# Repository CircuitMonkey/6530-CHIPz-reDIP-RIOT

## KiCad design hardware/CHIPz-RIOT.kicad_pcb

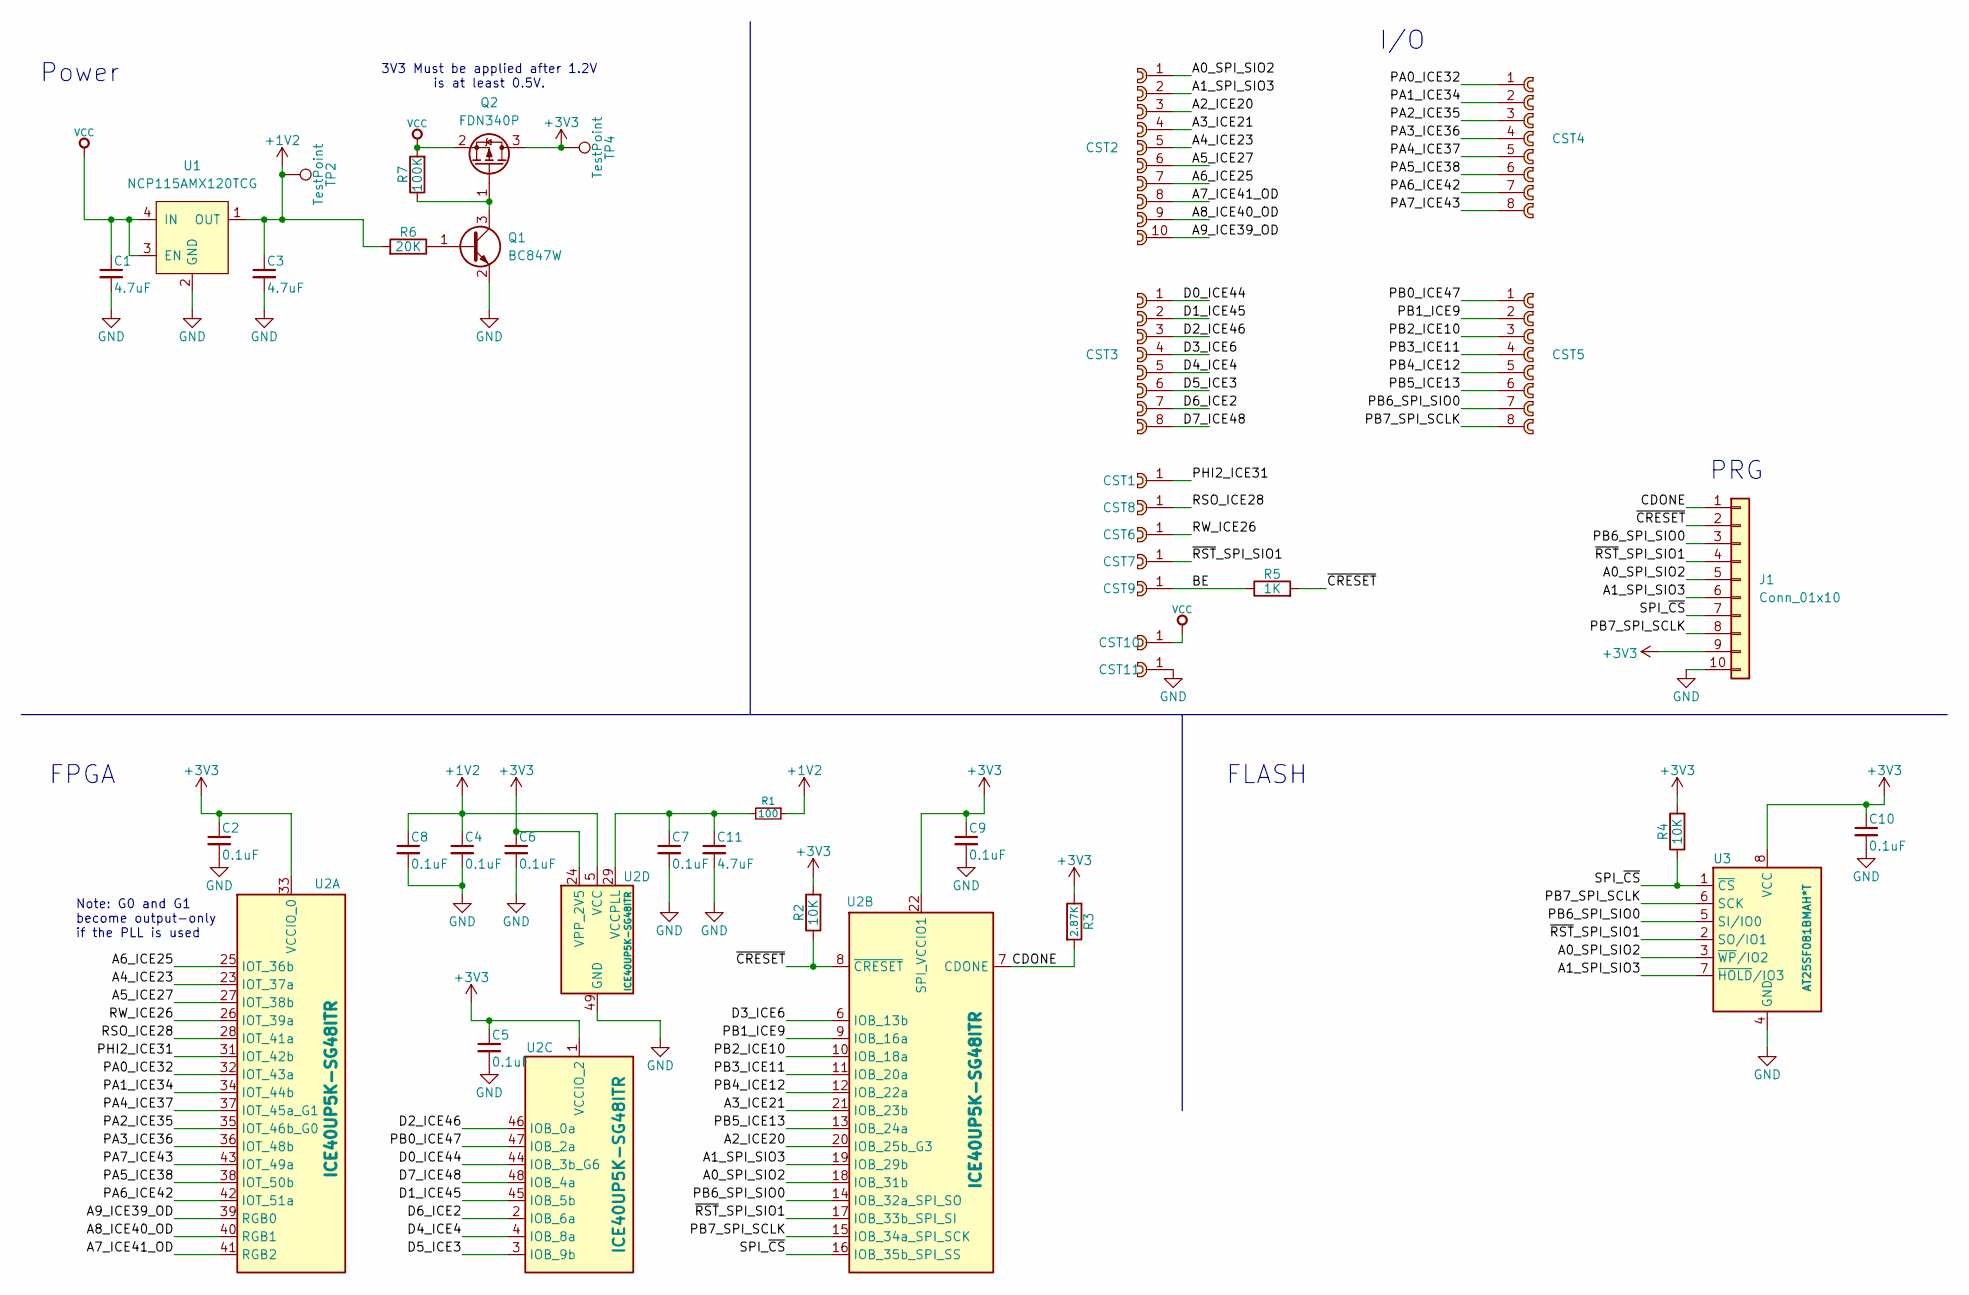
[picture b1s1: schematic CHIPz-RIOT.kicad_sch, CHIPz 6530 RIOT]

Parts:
C1, C3, C11: 4.7uF; C_0402_1005Metric_Pad0.74x0.62mm_HandSolder
C2, C4, C5, C6, C7, C8, C9, C10: 0.1uF; C_0402_1005Metric_Pad0.74x0.62mm_HandSolder
CST1, CST6, CST7, CST8, CST9, CST10, CST11: cast-2.0-01P
CST2: cast-2.0-10P
CST3, CST4, CST5: cast-2.0-08P
J1: Conn_01x10; JST_SHL_SM10B-SHLS-TF_1x10-1MP_P1.00mm_Horizontal
Q1: BC847W; SOT-323_SC-70
Q2: FDN340P; SOT-23
R1: 100; R_0402_1005Metric_Pad0.72x0.64mm_HandSolder
R2, R4: 10K; R_0402_1005Metric_Pad0.72x0.64mm_HandSolder
R3: 2.87K; R_0402_1005Metric_Pad0.72x0.64mm_HandSolder
R5: 1K; R_0402_1005Metric_Pad0.72x0.64mm_HandSolder
R6: 20K; R_0402_1005Metric_Pad0.72x0.64mm_HandSolder
R7: 100K; R_0402_1005Metric_Pad0.72x0.64mm_HandSolder
TP2, TP4: TestPoint; TestPoint_Pad_D1.00mm
U1: NCP115AMX120TCG; CASE_711AJ_1.0x1.0mm_P0.65mm
U2: ICE40UP5K-SG48ITR; QFN-48-1EP_7x7mm_P0.5mm_EP5.6x5.6mm
U3: AT25SF081BMAH*T; UDFN-8_EP_3x2_Pitch0.5mm

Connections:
+1V2: C3.1, C4.1, C8.1, R1.1, R6.2, TP2.1, U1.1 (OUT), U2.5 (VCC), U2.30 (VCC)
+3V3: C2.1, C5.1, C6.1, C9.1, C10.1, J1.9, Q2.3 (D), R2.2, R3.1, R4.2, TP4.1, U2.1 (VCCIO_2), U2.22 (SPI_VCCIO1), U2.24 (VPP_2V5), U2.33 (VCCIO_0), U3.8 (VCC)
/A0_SPI_SIO2: CST2.1, J1.5, U2.18 (IOB_31b), U3.3 (~WP/IO2)
/A1_SPI_SIO3: CST2.2, J1.6, U2.19 (IOB_29b), U3.7 (~HOLD/IO3)
/A2_ICE20: CST2.3, U2.20 (IOB_25b_G3)
/A3_ICE21: CST2.4, U2.21 (IOB_23b)
/A4_ICE23: CST2.5, U2.23 (IOT_37a)
/A5_ICE27: CST2.6, U2.27 (IOT_38b)
/A6_ICE25: CST2.7, U2.25 (IOT_36b)
/A7_ICE41_OD: CST2.8, U2.41 (RGB2)
/A8_ICE40_OD: CST2.9, U2.40 (RGB1)
/A9_ICE39_OD: CST2.10, U2.39 (RGB0)
/BE: CST9.1, R5.1
/CDONE: J1.1, R3.2, U2.7 (CDONE)
/D0_ICE44: CST3.1, U2.44 (IOB_3b_G6)
/D1_ICE45: CST3.2, U2.45 (IOB_5b)
/D2_ICE46: CST3.3, U2.46 (IOB_0a)
/D3_ICE6: CST3.4, U2.6 (IOB_13b)
/D4_ICE4: CST3.5, U2.4 (IOB_8a)
/D5_ICE3: CST3.6, U2.3 (IOB_9b)
/D6_ICE2: CST3.7, U2.2 (IOB_6a)
/D7_ICE48: CST3.8, U2.48 (IOB_4a)
/PA0_ICE32: CST4.1, U2.32 (IOT_43a)
/PA1_ICE34: CST4.2, U2.34 (IOT_44b)
/PA2_ICE35: CST4.3, U2.35 (IOT_46b_G0)
/PA3_ICE36: CST4.4, U2.36 (IOT_48b)
/PA4_ICE37: CST4.5, U2.37 (IOT_45a_G1)
/PA5_ICE38: CST4.6, U2.38 (IOT_50b)
/PA6_ICE42: CST4.7, U2.42 (IOT_51a)
/PA7_ICE43: CST4.8, U2.43 (IOT_49a)
/PB0_ICE47: CST5.1, U2.47 (IOB_2a)
/PB1_ICE9: CST5.2, U2.9 (IOB_16a)
/PB2_ICE10: CST5.3, U2.10 (IOB_18a)
/PB3_ICE11: CST5.4, U2.11 (IOB_20a)
/PB4_ICE12: CST5.5, U2.12 (IOB_22a)
/PB5_ICE13: CST5.6, U2.13 (IOB_24a)
/PB6_SPI_SIO0: CST5.7, J1.3, U2.14 (IOB_32a_SPI_SO), U3.5 (SI/IO0)
/PB7_SPI_SCLK: CST5.8, J1.8, U2.15 (IOB_34a_SPI_SCK), U3.6 (SCK)
/PHI2_ICE31: CST1.1, U2.31 (IOT_42b)
/RSO_ICE28: CST8.1, U2.28 (IOT_41a)
/RW_ICE26: CST6.1, U2.26 (IOT_39a)
/SPI_~CS: J1.7, R4.1, U2.16 (IOB_35b_SPI_SS), U3.1 (~CS)
/~CRESET: J1.2, R2.1, R5.2, U2.8 (~CRESET)
/~RST_SPI_SIO1: CST7.1, J1.4, U2.17 (IOB_33b_SPI_SI), U3.2 (SO/IO1)
GND: C1.2, C2.2, C3.2, C4.2, C5.2, C6.2, C7.2, C8.2, C9.2, C10.2, C11.2, CST11.1, J1.10, Q1.2 (E), U1.2 (GND), U2.49 (GND), U3.4 (GND)
unnamed: Q1.1 (B), R6.1
unnamed: Q1.3 (C), Q2.1 (G), R7.1
unnamed: C7.1, C11.1, R1.2, U2.29 (VCCPLL)
VCC: C1.1, CST10.1, Q2.2 (S), R7.2, U1.3 (EN), U1.4 (IN)

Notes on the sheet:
PRG
FLASH
FPGA
Power
3V3 Must be applied after 1.2V is at least 0.5V.
I/O
Note: G0 and G1 become output-only if the PLL is used

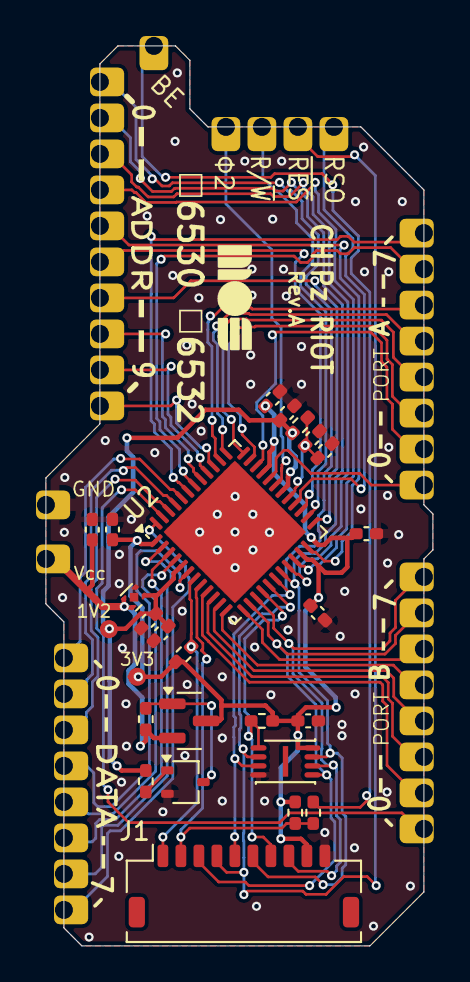
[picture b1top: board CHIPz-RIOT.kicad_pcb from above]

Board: 2 copper layers, 21.5 x 50.0 mm, 37 parts (0 on the bottom side), 49 nets.

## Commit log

2025-07-17 New version of reDIP-RIOT PCB, now CHIPz RIOT.
2025-07-17 Add 3D models for Chips and connector
2025-07-26 Add 3D model.
2025-09-07 Added assembly note/change.
2025-09-07 Add FPGA images.

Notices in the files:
hardware/CHIPz-RIOT.kicad_pcb:
© 2023 Dag Lem
Licensed under CERN-OHL-S v2 (https://ohwr.org/cern_ohl_s_v2.txt)
CERN-OHL-S v2
hardware/CHIPz-RIOT.kicad_sch:
© 2023 Dag Lem,  CHIPz version © 2025 Mark J Koch
